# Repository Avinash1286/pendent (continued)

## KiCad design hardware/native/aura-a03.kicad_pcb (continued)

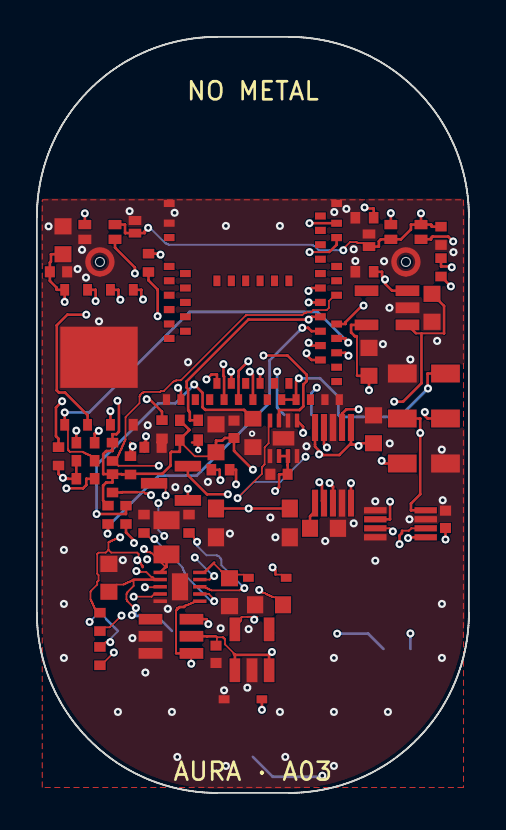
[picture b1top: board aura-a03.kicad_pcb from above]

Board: 4 copper layers, 24.0 x 42.0 mm, 61 parts (0 on the bottom side), 43 nets.

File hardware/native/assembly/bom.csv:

Reference,Quantity,MPN,Value,NativeFootprint,AssemblyStatus
U1,1,MDBT50Q-1MV2,nRF52840 BLE module,AURA_PCB:A03_U1,Candidate; dense assembly and supplier qualification pending
MK1,1,SPH0641LU4H-1,Left PDM microphone,AURA_PCB:A03_MK1,Candidate; dense assembly and supplier qualification pending
MK2,1,SPH0641LU4H-1,Right PDM microphone,AURA_PCB:A03_MK2,Candidate; dense assembly and supplier qualification pending
U2,1,W25N01GVZEIG,1Gbit SPI NAND /128MiB,AURA_PCB:A03_U2,Candidate; dense assembly and supplier qualification pending
U3,1,BQ25185DLHR,53mA Li-ion powerpath charger,AURA_PCB:A03_U3,Candidate; dense assembly and supplier qualification pending
U4,1,TLV75530PDBVR,3.0V system regulator,AURA_PCB:A03_U4,Candidate; dense assembly and supplier qualification pending
U5,1,MAX17048G+T10,ModelGauge fuel gauge,AURA_PCB:A03_U5,Candidate; dense assembly and supplier qualification pending
U6,1,DRV2605LDGSR,LRA closed-loop haptics,AURA_PCB:A03_U6,Candidate; dense assembly and supplier qualification pending
U7,1,TLV75530PDBVR,Recording-only3V microphone regulator,AURA_PCB:A03_U7,Candidate; dense assembly and supplier qualification pending
U8,1,SN74LVC2G125DCUR,Ioff protected PDM isolation,AURA_PCB:A03_U8,Candidate; dense assembly and supplier qualification pending
U9,1,TLV6700DDCR,Independent charge hot cutoff,AURA_PCB:A03_U9,Candidate; dense assembly and supplier qualification pending
Q1,1,DMG2302UK-7,Default-off charge permission,AURA_PCB:A03_Q1,Candidate; dense assembly and supplier qualification pending
SW1,1,JS202011JCQN,Mechanical DPDT microphone OFF,AURA_PCB:A03_SW1,Candidate; dense assembly and supplier qualification pending
SW2,1,KMR211NGULCLFS,Flush face record / stop,AURA_PCB:A03_SW2,Candidate; dense assembly and supplier qualification pending
D1,1,BAT54WS-7-F,Reverse-dock Schottky,AURA_PCB:A03_D1,Candidate; dense assembly and supplier qualification pending
D2,1,"PESD5V0S1BA,115",Dock transient suppression,AURA_PCB:A03_D2,Candidate; dense assembly and supplier qualification pending
LED1,1,LTST-C190KFKT,Amber hard recording indicator,AURA_PCB:A03_LED1,Candidate; dense assembly and supplier qualification pending
R1,1,RC0402FR-075K62L,5.62k,AURA_PCB:A03_R1,Candidate; dense assembly and supplier qualification pending
R2,1,RC0402FR-0724KL,24k,AURA_PCB:A03_R2,Candidate; dense assembly and supplier qualification pending
R3,1,RC0402FR-0710KL,10k,AURA_PCB:A03_R3,Candidate; dense assembly and supplier qualification pending
R4,1,RC0402FR-0710KL,10k,AURA_PCB:A03_R4,Candidate; dense assembly and supplier qualification pending
R5,1,RC0402FR-0710KL,10k,AURA_PCB:A03_R5,Candidate; dense assembly and supplier qualification pending
R6,1,RC0402FR-074K7L,4.7k,AURA_PCB:A03_R6,Candidate; dense assembly and supplier qualification pending
R7,1,RC0402FR-074K7L,4.7k,AURA_PCB:A03_R7,Candidate; dense assembly and supplier qualification pending
R8,1,RC0402FR-07100KL,100k,AURA_PCB:A03_R8,Candidate; dense assembly and supplier qualification pending
R9,1,RC0402FR-07100KL,100k,AURA_PCB:A03_R9,Candidate; dense assembly and supplier qualification pending
R10,1,RC0402FR-07100KL,100k,AURA_PCB:A03_R10,Candidate; dense assembly and supplier qualification pending
R11,1,RC0402FR-0710KL,10k,AURA_PCB:A03_R11,Candidate; dense assembly and supplier qualification pending
R13,1,RC0402FR-0710KL,10k,AURA_PCB:A03_R13,Candidate; dense assembly and supplier qualification pending
R14,1,RC0402FR-071KL,1k,AURA_PCB:A03_R14,Candidate; dense assembly and supplier qualification pending
R15,1,RC0402FR-07100KL,100k,AURA_PCB:A03_R15,Candidate; dense assembly and supplier qualification pending
R16,1,RC0402FR-0733RL,33,AURA_PCB:A03_R16,Candidate; dense assembly and supplier qualification pending
R17,1,RC0402FR-0733RL,33,AURA_PCB:A03_R17,Candidate; dense assembly and supplier qualification pending
R18,1,RC0402FR-0710KL,10k,AURA_PCB:A03_R18,Candidate; dense assembly and supplier qualification pending
R19,1,RC0402FR-0710KL,10k,AURA_PCB:A03_R19,Candidate; dense assembly and supplier qualification pending
R20,1,RC0402FR-0710KL,10k,AURA_PCB:A03_R20,Candidate; dense assembly and supplier qualification pending
R21,1,RC0402FR-0710KL,10k,AURA_PCB:A03_R21,Candidate; dense assembly and supplier qualification pending
R22,1,RC0402FR-073K3L,3.3k,AURA_PCB:A03_R22,Candidate; dense assembly and supplier qualification pending
R23,1,RC0402FR-0710KL,10k,AURA_PCB:A03_R23,Candidate; dense assembly and supplier qualification pending
C1,1,C0402C104K4RACTU,100nF,AURA_PCB:A03_C1,Candidate; dense assembly and supplier qualification pending
C2,1,C0603C475K8PACTU,4.7uF,AURA_PCB:A03_C2,Candidate; dense assembly and supplier qualification pending
C3,1,939113424610-T3N,100nF silicon,AURA_PCB:A03_C3,Candidate; dense assembly and supplier qualification pending
C4,1,939113424610-T3N,100nF silicon,AURA_PCB:A03_C4,Candidate; dense assembly and supplier qualification pending
C5,1,C0402C104K4RACTU,100nF,AURA_PCB:A03_C5,Candidate; dense assembly and supplier qualification pending
C6,1,C0603C475K8PACTU,4.7uF,AURA_PCB:A03_C6,Candidate; dense assembly and supplier qualification pending
C7,1,C0603C225K8RACTU,2.2uF,AURA_PCB:A03_C7,Candidate; dense assembly and supplier qualification pending
C8,1,C0603C475K8PACTU,4.7uF,AURA_PCB:A03_C8,Candidate; dense assembly and supplier qualification pending
C9,1,C0805C106K8PACTU,10uF,AURA_PCB:A03_C9,Candidate; dense assembly and supplier qualification pending
C10,1,C0603C225K8RACTU,2.2uF,AURA_PCB:A03_C10,Candidate; dense assembly and supplier qualification pending
C11,1,C0402C104K4RACTU,100nF,AURA_PCB:A03_C11,Candidate; dense assembly and supplier qualification pending
C12,1,C0603C105K4RACTU,1uF,AURA_PCB:A03_C12,Candidate; dense assembly and supplier qualification pending
C13,1,C0603C105K4RACTU,1uF,AURA_PCB:A03_C13,Candidate; dense assembly and supplier qualification pending
C14,1,C0603C105K4RACTU,1uF,AURA_PCB:A03_C14,Candidate; dense assembly and supplier qualification pending
C15,1,C0603C105K4RACTU,1uF,AURA_PCB:A03_C15,Candidate; dense assembly and supplier qualification pending
C16,1,C0402C104K4RACTU,100nF,AURA_PCB:A03_C16,Candidate; dense assembly and supplier qualification pending
C17,1,C0402C103K5RACTU,10nF,AURA_PCB:A03_C17,Candidate; dense assembly and supplier qualification pending
C18,1,C0402C104K4RACTU,100nF,AURA_PCB:A03_C18,Candidate; dense assembly and supplier qualification pending
